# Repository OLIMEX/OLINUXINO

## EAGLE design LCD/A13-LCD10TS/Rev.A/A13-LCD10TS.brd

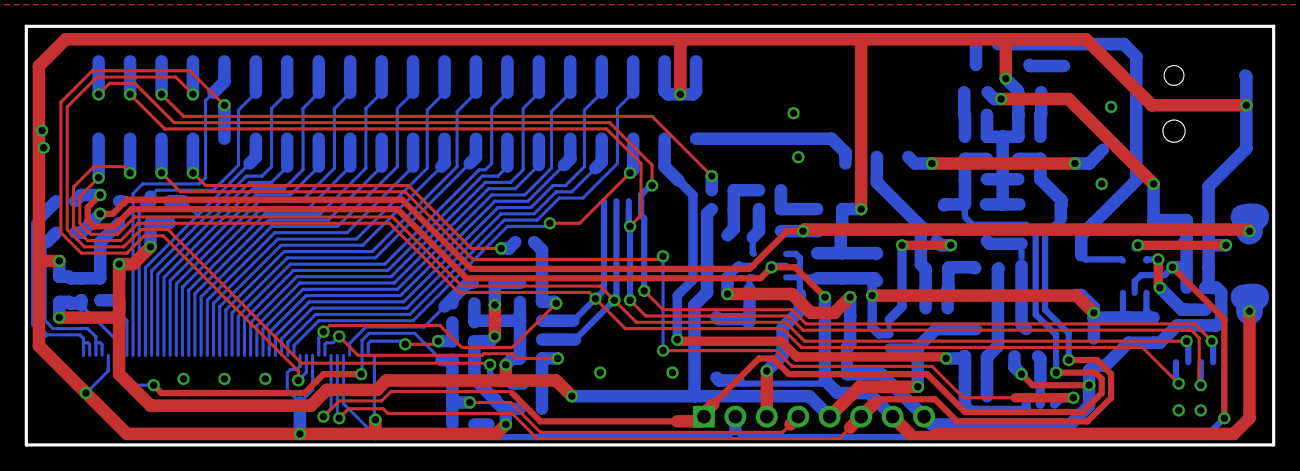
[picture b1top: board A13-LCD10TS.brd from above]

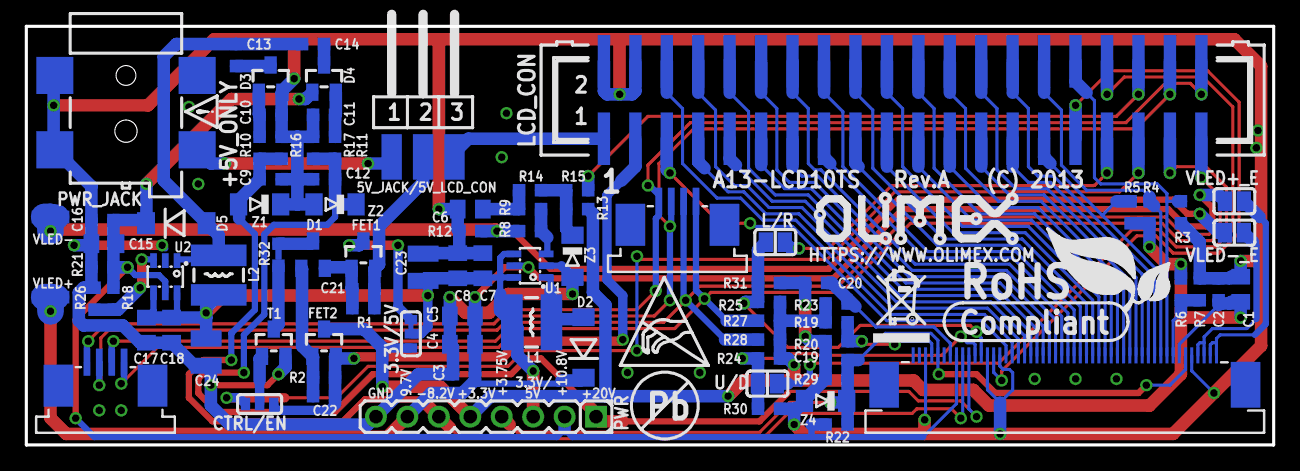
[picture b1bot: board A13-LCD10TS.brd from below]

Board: 2 copper layers, 100.8 x 33.8 mm, 91 parts (90 on the bottom side), 72 nets.

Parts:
3.3V/5V: 5V:Close/3.3V:Open; SJ_2_SMALL_12_TIED
5V_JACK/5V_LCD_CON: H-WX-1x3; HN1X3-SMD
C1, C7, C8, C17, C18: 22uF/6.3V; C0805_5MIL_DWS
C2, C3, C9, C10, C11, C12, C13, C14, C16, C19, C20: 100nF; C0603_DWS
C4, C5: 1uF/25V; C0805_5MIL_DWS
C6, C15: 10uF/16V; C0805_5MIL_DWS
C21, C22: NA; C0603_DWS
C23, C24: NA(100uF/16V); C-SMD5X11-M
CTRL/EN: CTRL:Close/EN:Open; SJ_2_SMALL
D1: BAT54C; SOT23C
D2, D5: 1N5819/SS14; MLL-41
D3, D4: BAT54S; SOT23C(BAT54S)
FET1, FET2: IRLML6402; SOT23
L1, L2: 4.7uH/1.15A/DCR<0.1R/CD43; CD42(43)
L/R: Open; SJ
LCD: F101T50+(FPV-WZA21-50-LF)+(FPA-WZB25-04-LF); LCD10"_TOUCH(F101T50)
LCD_CON: ML40-GBH-254-SMT-40; ML40-MALE(GBH-254-SMT-40)
PWR: NA(HN1X8); HN1X8
PWR_JACK: DCJ-W54R-20-LF; PWR-JACK-SMD
R1, R2, R7, R19, R23, R25, R30: 10k; R0603_5MIL_DWS
R3, R4, R5, R6, R20, R24, R27, R28, R31: NA; R0603_5MIL_DWS
R8: 2.2k; R0603_5MIL_DWS
R9, R21: 20k; R0603_5MIL_DWS
R10, R11, R22, R26: 1.05k/1%; R0603_5MIL_DWS
R12: 1.1R; R0603_5MIL_DWS
R13, R14: 4.7k; R0603_5MIL_DWS
R15: 220R; R0603_5MIL_DWS
R16, R17, R18: 56.2k/1%; R0603_5MIL_DWS
R29: 562R/1%; R0603_5MIL_DWS
R32: 0R(Board_Mounted); 0603_0R
T1: DTC114YKA; SOT-23
U1, U2: AP3031KTR-G1; SOT23-6
U$4: ATTENTION_SMALL
U$8: OLIMEX1_V
U$9: PB
U$10: ESD_SYMBOL
U$11: RECYCLE_BIN1/8
U$12: ROHS
U/D: Open; SJ
VLED+: TESTPAD120X40; SMD120X40
VLED+_E: NA; SJ
VLED-: TESTPAD120X40; SMD120X40
VLED-_E: NA; SJ
Z1: BZV55C8V2; MINI-MELF
Z2: BZV55C20; MINI-MELF
Z3: NA(BZV55C3V0); MINI-MELF
Z4: NA(BZV55C3V9); MINI-MELF

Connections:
+5V: 3.3V/5V.2, C7.2, C8.2, C17.2, C18.2, C23.+, C24.+, L1.1, L2.1, PWR.3, U1.4, U1.6, U2.4, U2.6
+12V: C15.1, C16.1, D4.1, D5.K, LCD.43, PWR.2, R18.2, R21.2, R22.1, U2.5
+15V: C12.1, LCD.41, PWR.1, R11.1, R17.2, Z2.1
-24V: C9.1, LCD.42, PWR.6, R10.1, R16.2, Z1.2
GND: C1.2, C2.2, C3.2, C4.2, C5.2, C6.2, C7.1, C8.1, C9.2, C10.2, C11.2, C12.2, C15.2, C16.2, C17.1, C18.1, C19.2, C20.2, C23.-, C24.-, D3.2, LCD.5, LCD.36, LCD.38, LCD.48, LCD_CON.2, LCD_CON.4, PWR.8, PWR_JACK.2, PWR_JACK.3, R3.1, R7.1, R12.2, R16.1, R17.1, R20.1, R21.1, R26.2, R29.2, R30.2, R31.2, T1.2, U1.2, Z1.1, Z2.2, Z3.2, Z4.2
LCD_B0: LCD.19, LCD_CON.21
LCD_B1: LCD.18, LCD_CON.22
LCD_B2: LCD.17, LCD_CON.23
LCD_B3: LCD.16, LCD_CON.24
LCD_B4: LCD.15, LCD_CON.25
LCD_B5: LCD.14, LCD_CON.26
LCD_B6: LCD.13, LCD_CON.27
LCD_B7: LCD.12, LCD_CON.28
LCD_BKL: LCD_CON.36, R15.1
LCD_CLK: LCD.37, LCD_CON.31
LCD_DE: LCD.9, LCD_CON.32, R3.2
LCD_G0: LCD.27, LCD_CON.13
LCD_G1: LCD.26, LCD_CON.14
LCD_G2: LCD.25, LCD_CON.15
LCD_G3: LCD.24, LCD_CON.16
LCD_G4: LCD.23, LCD_CON.17
LCD_G5: LCD.22, LCD_CON.18
LCD_G6: LCD.21, LCD_CON.19
LCD_G7: LCD.20, LCD_CON.20
LCD_HSYNC: LCD.11, LCD_CON.29, R5.2
LCD_L/R: L/R.1, LCD.39, R25.2, R31.1
LCD_PWRE: CTRL/EN.3, LCD_CON.35
LCD_R0: LCD.35, LCD_CON.5
LCD_R1: LCD.34, LCD_CON.6
LCD_R2: LCD.33, LCD_CON.7
LCD_R3: LCD.32, LCD_CON.8
LCD_R4: LCD.31, LCD_CON.9
LCD_R5: LCD.30, LCD_CON.10
LCD_R6: LCD.29, LCD_CON.11
LCD_R7: LCD.28, LCD_CON.12
LCD_U/D: LCD.40, R24.2, R30.1, U/D.1
LCD_VSYNC: LCD.10, LCD_CON.30, R4.2
unnamed: LCD.8, R6.2, R7.2
unnamed: C14.2, D4.3
unnamed: C22.1, CTRL/EN.1, FET2.2, LCD_CON.3, R2.2
unnamed: C11.1, D4.2, R11.2
unnamed: R8.1, R9.1, U1.3
unnamed: C10.1, D3.1, R10.2
unnamed: 5V_JACK/5V_LCD_CON.2, C21.1, FET1.2, R1.2
unnamed: C22.2, D1.1, FET2.1, R2.1
unnamed: C21.2, D1.2, FET1.1, R1.1
unnamed: C13.1, D3.3
unnamed: R32.2, T1.3
unnamed: C6.1, R9.2, R14.2
unnamed: D2.A, L1.2, U1.1
unnamed: R13.1, R14.1, R15.2, Z3.1
unnamed: L/R.2, LCD_CON.33
unnamed: CTRL/EN.2, T1.1
unnamed: LCD_CON.34, U/D.2
unnamed: 3.3V/5V.1, FET1.3
unnamed: D1.3, R32.1
unnamed: 5V_JACK/5V_LCD_CON.3, LCD_CON.1
unnamed: LCD.1, LCD.2, VLED+_E.1
unnamed: 5V_JACK/5V_LCD_CON.1, PWR_JACK.1
unnamed: LCD.3, LCD.4, VLED-_E.1
unnamed: LCD.47, R19.2, R20.2
unnamed: C13.2, C14.1, D5.A, L2.2, U2.1
unnamed: R18.1, R26.1, U2.3
RESET: C20.1, LCD.44, R23.2
TPX1: LCD.51, LCD.55, LCD_CON.37, R27.2
TPX2: LCD.53, LCD.57, LCD_CON.38
TPY1: LCD.52, LCD.56, LCD_CON.39, R28.2
TPY2: LCD.54, LCD.58, LCD_CON.40
VCC: 3.3V/5V.3, C1.1, C2.1, FET2.3, LCD.7, PWR.5, R4.1, R5.1, R6.1, R13.2, R19.1, R23.1, R24.1, R25.1, R27.1, R28.1
VCOM: C19.1, LCD.6, LCD.46, PWR.4, R22.2, R29.1, Z4.1
VLED+: C3.1, C4.1, C5.1, D2.K, PWR.7, U1.5, VLED+.1, VLED+_E.2
VLED-: R8.2, R12.1, VLED-.1, VLED-_E.2

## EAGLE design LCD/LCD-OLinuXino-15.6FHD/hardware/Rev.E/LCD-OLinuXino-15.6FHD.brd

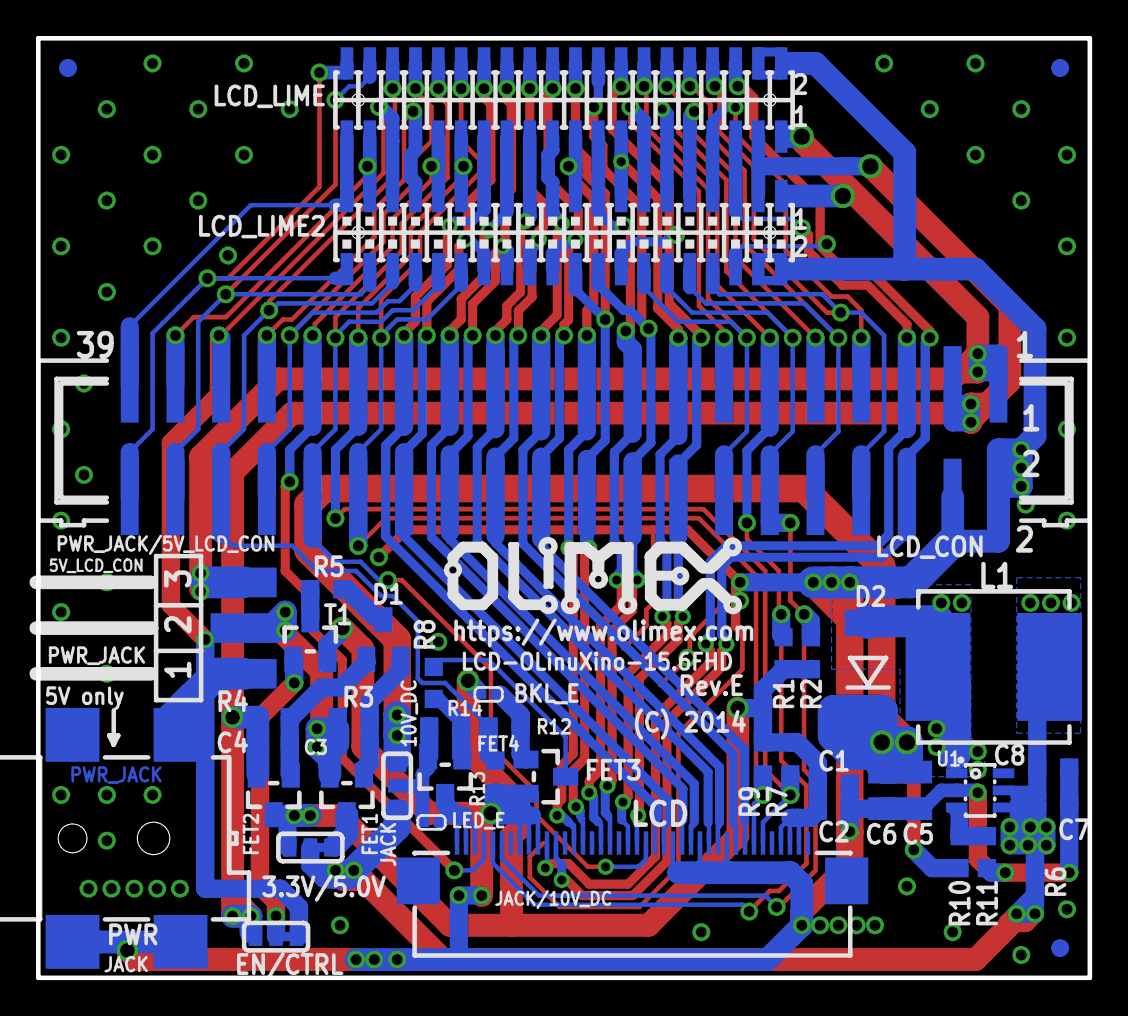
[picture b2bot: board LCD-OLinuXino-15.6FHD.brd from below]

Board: 2 copper layers, 58.4 x 52.2 mm, 50 parts (45 on the bottom side), 58 nets.

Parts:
3.3V/5.0V: 3.3V:Open/5.0V:Close; SJ_2_SMALL_23_TIED
BKL_E: open; SJ_1_THE_SMALLEST
C1, C2, C3, C7, C8: 22uF/6.3V; C0603_DWS
C4: NA; C0603_DWS
C5, C6: 10uF/16V; C0805_5MIL_DWS
D1: BAT54C; SOT23C
D2: 1N5822/SS34/SMA; MELF-MLL41
EN/CTRL: EN:Open/CTRL:Close; SJ_2_SMALL_23_TIED
FET1, FET2, FET4: IRLML6402; SOT23
FET3: BSS138; SOT23
JACK/10V_DC: PWR_JACK:Open/10V_DCDC:Close; SJ_2_SMALL
L1: 2.2uH/3A/YS75/7x8; 8X8MM_3131
LCD: LCD15.6''(B156XW04_V5)FPV-WZA21-40-LF; LCD_15.6''
LCD_CON: ML40-GBH-254-SMT-40; ML40-MALE(GBH-254-SMT-40)
LCD_LIME: ML40-GPH127SMT-02X20; YA-V36P-2X20-LF
LCD_LIME2: ML40-GPH127SMT-02X20; GPH127SMT-02X20(PA-V16X-2X20-LF)
LED_E: open; SJ_1_THE_SMALLEST
PWR_JACK: DCJ-W54R-20-LF; PWR-JACK-SMD
PWR_JACK/5V_LCD_CON: H-WX-1x3; HN1X3-SMD
R1, R2, R4, R13: 10k; R0603_5MIL_DWS
R3, R10: 18.2k/1%; R0603_5MIL_DWS
R5, R11, R14: 1.1k/1%; R0603_5MIL_DWS
R6: 0R(board_munted); 0603_0R
R7, R9: NA(4.7k); R0603_5MIL_DWS
R8, R12: 560R; R0603_5MIL_DWS
T1: DTC114YKA; SOT-23
U1: SY7208(SOT23-6); SOT23-6
U$1, U$2, U$3: FIDUCIAL; FIDUCIAL-1X3
U$5: ROHS
U$6: PB
U$8: OLIMEX1_V
U$10: ESD_SYMBOL
U$11: RECYCLE_BIN1/8

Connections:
3.3VDC: C4.1, EN/CTRL.1, FET2.2, LCD_CON.3, LCD_LIME.3, LCD_LIME2.3, R4.2
5VDC: C3.1, FET1.2, PWR_JACK/5V_LCD_CON.2, R3.2
+5V: 3.3V/5.0V.2, JACK/10V_DC.1, R6.2
+12V: C5.1, C6.1, D2.1, JACK/10V_DC.3, R10.2
CLK_EDID: LCD.6, LCD_CON.29, LCD_LIME.29, LCD_LIME2.29, R7.2
DAT_EDID: LCD.7, LCD_CON.30, LCD_LIME.30, LCD_LIME2.30, R9.2
DCR_EN: LCD.37, LCD_CON.31, LCD_LIME.31, LCD_LIME2.31
GND: C1.2, C2.2, C5.2, C6.2, C7.2, C8.2, FET3.2, LCD.10, LCD.13, LCD.16, LCD.31, LCD.32, LCD.33, LCD_CON.2, LCD_CON.4, LCD_LIME.2, LCD_LIME.4, LCD_LIME2.2, LCD_LIME2.4, PWR_JACK.2, PWR_JACK.3, R11.2, R13.1, T1.2, U1.2
IMG_EN: LCD.19, LCD_CON.32, LCD_LIME.32, LCD_LIME2.32
LCD_BKL: LCD_CON.36, LCD_LIME.36, LCD_LIME2.36, R12.1, R13.2
LCD_PWRE: EN/CTRL.3, LCD_CON.35, LCD_LIME.35, LCD_LIME2.35
LVDS0_VN0: LCD.8, LCD_CON.22, LCD_LIME.22, LCD_LIME2.22
LVDS0_VN1: LCD.11, LCD_CON.24, LCD_LIME.24, LCD_LIME2.24
LVDS0_VN2: LCD.14, LCD_CON.26, LCD_LIME.26, LCD_LIME2.26
LVDS0_VNC: LCD.17, LCD_CON.28, LCD_LIME.28, LCD_LIME2.28
LVDS0_VP0: LCD.9, LCD_CON.21, LCD_LIME.21, LCD_LIME2.21
LVDS0_VP1: LCD.12, LCD_CON.23, LCD_LIME.23, LCD_LIME2.23
LVDS0_VP2: LCD.15, LCD_CON.25, LCD_LIME.25, LCD_LIME2.25
LVDS0_VPC: LCD.18, LCD_CON.27, LCD_LIME.27, LCD_LIME2.27
unnamed: 3.3V/5.0V.3, FET1.3
unnamed: FET4.2, JACK/10V_DC.2, LED_E.1, R14.1
unnamed: FET4.3, LCD.38, LCD.39, LCD.40, LED_E.2
unnamed: BKL_E.1, FET3.1, R12.2
unnamed: LCD_CON.7, LCD_LIME.7, LCD_LIME2.7
unnamed: LCD_CON.9, LCD_LIME.9, LCD_LIME2.9
unnamed: LCD_CON.13, LCD_LIME.13, LCD_LIME2.13
unnamed: C4.2, D1.1, FET2.1, R4.1
unnamed: C3.2, D1.2, FET1.1, R3.1
unnamed: LCD_CON.33, LCD_LIME.33, LCD_LIME2.33
unnamed: R5.1, T1.3
unnamed: LCD_CON.37, LCD_LIME.37, LCD_LIME2.37
unnamed: LCD_CON.39, LCD_LIME.39, LCD_LIME2.39
unnamed: LCD_CON.8, LCD_LIME.8, LCD_LIME2.8
unnamed: LCD_CON.10, LCD_LIME.10, LCD_LIME2.10
unnamed: EN/CTRL.2, T1.1
unnamed: LCD_CON.14, LCD_LIME.14, LCD_LIME2.14
unnamed: LCD_CON.34, LCD_LIME.34, LCD_LIME2.34
unnamed: D1.3, R5.2
unnamed: LCD_CON.1, LCD_LIME.1, LCD_LIME2.1, PWR_JACK/5V_LCD_CON.3
unnamed: LCD_CON.38, LCD_LIME.38, LCD_LIME2.38
unnamed: PWR_JACK.1, PWR_JACK/5V_LCD_CON.1
unnamed: LCD_CON.40, LCD_LIME.40, LCD_LIME2.40
unnamed: C7.1, C8.1, L1.2, R6.1, U1.4, U1.5
unnamed: FET4.1, R8.1, R14.2
unnamed: FET3.3, R8.2
unnamed: D2.2, L1.1, U1.1
unnamed: R10.1, R11.1, U1.3
RXE0+: LCD.21, LCD_CON.15, LCD_LIME.15, LCD_LIME2.15
RXE0-: LCD.20, LCD_CON.16, LCD_LIME.16, LCD_LIME2.16
RXE1+: LCD.24, LCD_CON.17, LCD_LIME.17, LCD_LIME2.17
RXE1-: LCD.23, LCD_CON.18, LCD_LIME.18, LCD_LIME2.18
RXE2+: LCD.27, LCD_CON.19, LCD_LIME.19, LCD_LIME2.19
RXE2-: LCD.26, LCD_CON.20, LCD_LIME.20, LCD_LIME2.20
RXEC+: LCD.30, LCD_CON.5, LCD_LIME.5, LCD_LIME2.5
RXEC-: LCD.29, LCD_CON.6, LCD_LIME.6, LCD_LIME2.6
VCC: 3.3V/5.0V.1, BKL_E.2, C1.1, C2.1, FET2.3, LCD.2, LCD.3, LCD.4, R1.2, R2.1, R7.1, R9.1
VLED_EN: LCD.36, LCD_CON.11, LCD_LIME.11, LCD_LIME2.11, R1.1
VPWM_EN: LCD.35, LCD_CON.12, LCD_LIME.12, LCD_LIME2.12, R2.2

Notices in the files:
LCD/A13-LCD10TS/Rev.A/A13-LCD10TS.brd:
(C) 2013
LCD/LCD-OLinuXino-15.6FHD/hardware/Rev.E/LCD-OLinuXino-15.6FHD.brd:
(C) 2014
